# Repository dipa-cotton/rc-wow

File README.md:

# rc-wow
custom RC Car Radio, with an LR1121 for dual-band access! I made this because I have a broken RC Car at my home, and the radio system was quite outdated so having a more enhanced radio system will allow me to control the car from farther away!
## project overview
this project contains an LR1121, ESP32, a microSD card, a USB-C receptacle, a spot for an OLED, and a spot to add a radio antenna, as well as other features to switch between frequencies and control power so it works both battery-powered and when plugged in.
## how it works
It is controlled by an esp32 and lr1121, with the espP32 serving as the microcontroller to take charge of all input and the lr1121 allowing the user to switch between different frequencies. There are ICs for this "switching" function. there is also a USB C receptical for input and control as well as a microSD card to log things that happen. The coax cable port is for the antenna. Resistors, decoupling capacitors, and Schottky diodes are used to prevent the board from exploding. The buttons are for reset and boot. There's an opening for an OLED display.
## pictures

## bom

| Part | Purpose | Qty | Unit Price | Total | Vendor |
|---|---|---:|---:|---:|---|
| [Battery Pack](https://www.aliexpress.us/item/3256807960114360.html) | Battery | 1 | $0.50 | $0.50 | AliExpress |
| [SD Card Reader](https://www.mouser.com/en/ProductDetail/Wurth-Elektronik/693072010801) | SD card reader | 1 | $3.50 | $3.50 | Mouser |
| [USB-C Receptacle](https://www.digikey.com/en/products/detail/gct/USB4085-GF-A/9859662) | USB connection | 1 | $1.00 | $1.00 | DigiKey |
| [Schottky Diode](https://www.aliexpress.us/item/3256808944462819.html) | Signal clearance | 1 | $3.50 | $3.50 | AliExpress |
| [Ferrite Bead](https://www.digikey.com/en/products/detail/laird-signal-integrity-products/28C0236-0JW-10/806596) | Ferrite bead | 1 | $1.10 | $1.10 | DigiKey |
| [0900FM15K0039001E](https://www.digikey.com/en/products/detail/johanson-technology-inc/0900FM15K0039001E/16639329) | Frequency switching | 2 | $0.50 | $1.00 | DigiKey |
| [0900DP15A2450001E](https://www.digikey.com/en/products/detail/johanson-technology-inc/0900DP15A2450001E/7943531) | Frequency switching | 1 | $1.00 | $1.00 | DigiKey |
| [ESP32-S3-WROOM-1-N8R8](https://www.digikey.com/en/products/detail/espressif-systems/ESP32-S3-WROOM-1-N8R8/15295891) | Main controller | 1 | $7.00 | $7.00 | DigiKey |
| [PE4259](https://www.digikey.com/en/products/detail/psemi/4259-63/2614473) | Frequency switching | 3 | $1.00 | $3.00 | DigiKey |
| [XC6220B331MR-G](https://www.digikey.com/en/products/detail/torex-semiconductor-ltd/XC6220B331MR-G/2138177) | Power regulation | 1 | $1.00 | $1.00 | DigiKey |
| [LR1121IMLTRT](https://www.digikey.com/en/products/detail/semtech-corporation/LR1121IMLTRT/17874420) | Frequency switching | 1 | $8.50 | $8.50 | DigiKey |
| [PMOS](https://www.digikey.com/ordering/shoppingcart) | Switching | 1 | $1.00 | $1.00 | DigiKey |
| [Crystals](https://www.digikey.com/en/products/detail/ecs-inc/ECS-320-8-36B-CKY-TR/9838841) | Oscillator | 2 | $1.00 | $2.00 | DigiKey |
| [OLED Display](https://www.aliexpress.us/item/3256812744946971.html) | Display | 1 | $3.00 | $3.00 | AliExpress |
| [Coaxial Cable Connector](https://www.digikey.com/en/products/detail/joymax-electronics/CT-SAD010XM/27545740) | Antenna connector | 1 | $2.50 | $2.50 | DigiKey |
| [Dual-Band Antenna](https://radiomasterrc.com/products/dual-band-2-4ghz-sub-g-900mhz-antenna) | Antenna | 1 | $15.00 | $15.00 | RadioMaster |
| [PCB](https://jlcpcb.com) | PCB for all components | 1 | $13.00 | $13.00 | JLCPCB |
| **Parts Subtotal** | — | — | — | **$67.60** | — |
| **Tax & Shipping** | — | — | — | **$0.00** | — |
| **Grand Total** | — | — | — | **$67.60** | — |
## notes
this should hopefully work! i had to calculate impedance for the RF traces and such, and it should work fine. however, updates may be pushed and future versions may be made :D also i have a HAM radio license so double check that things are legal on your end.

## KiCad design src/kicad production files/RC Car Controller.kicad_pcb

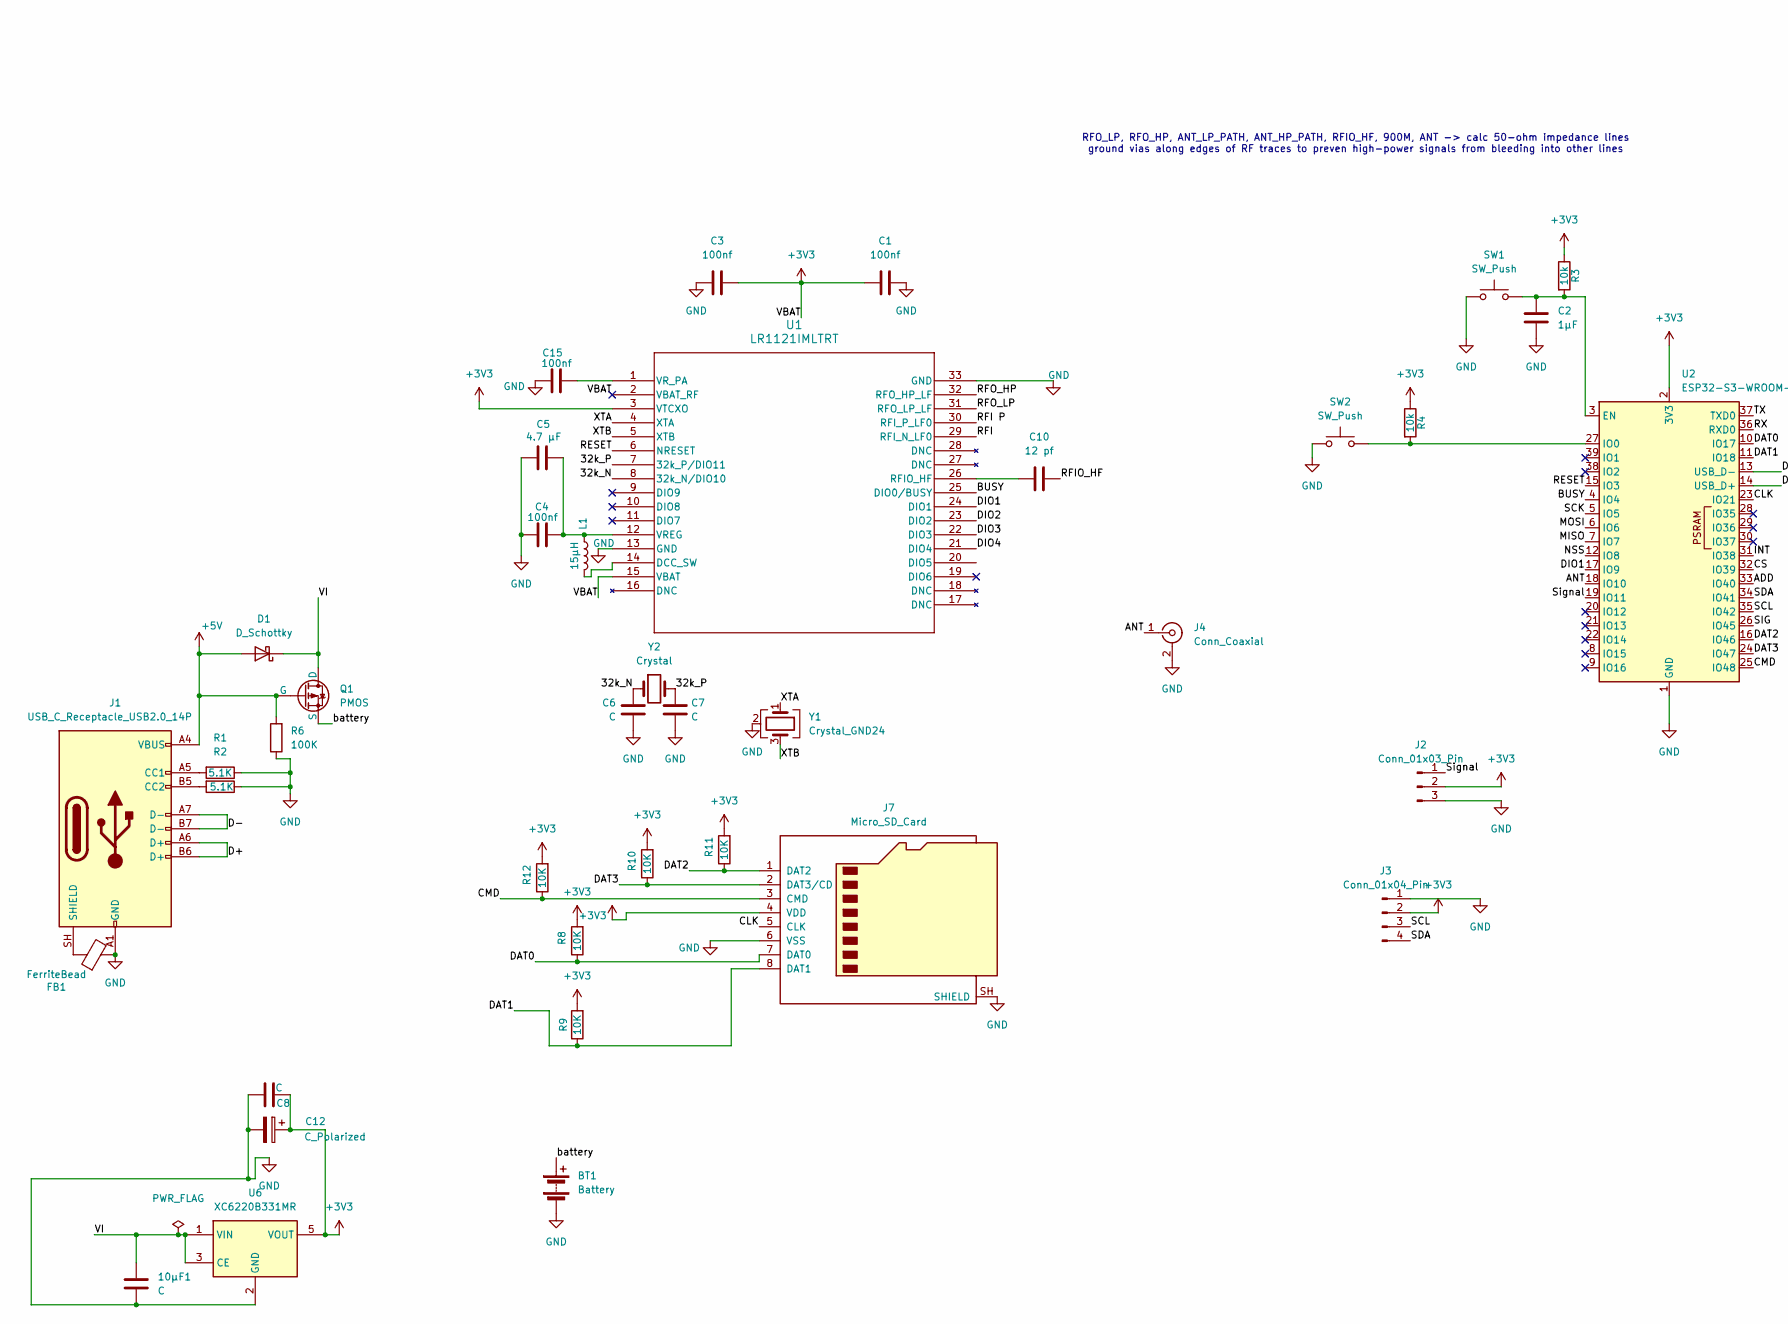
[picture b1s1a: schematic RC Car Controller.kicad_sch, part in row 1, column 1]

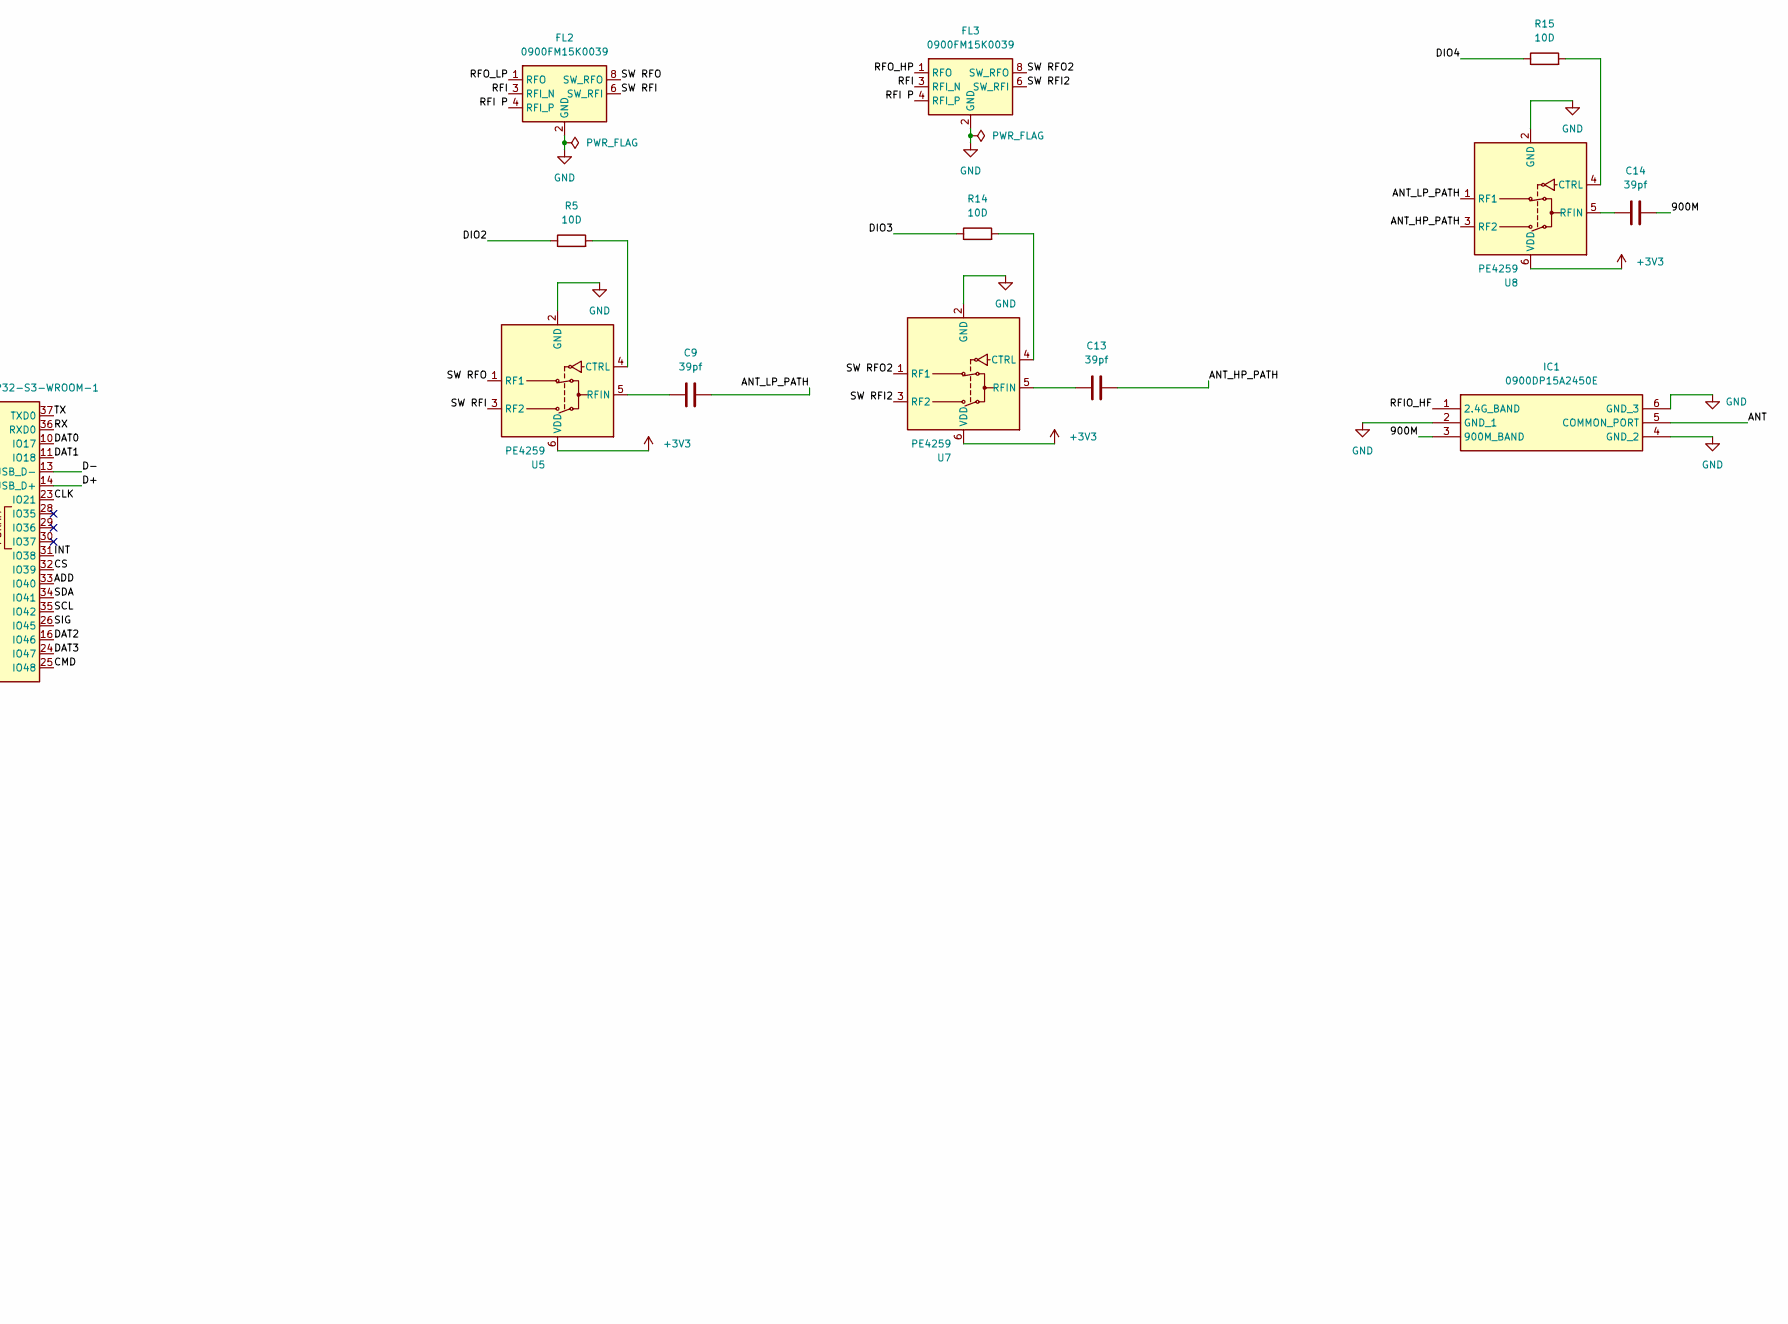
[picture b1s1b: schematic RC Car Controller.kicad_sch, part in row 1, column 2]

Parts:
10µF1: C; C_0402_1005Metric_Pad0.74x0.62mm_HandSolder
BT1: Battery; BatteryHolder_Keystone_2462_2xAA
C1, C3, C4, C15: 100nf; C_0402_1005Metric_Pad0.74x0.62mm_HandSolder
C2: 1µF; C_0402_1005Metric_Pad0.74x0.62mm_HandSolder
C5: 4.7 µF; C_0402_1005Metric_Pad0.74x0.62mm_HandSolder
C6, C7, C8: C; C_0402_1005Metric_Pad0.74x0.62mm_HandSolder
C9, C13, C14: 39pf; C_0402_1005Metric_Pad0.74x0.62mm_HandSolder
C10: 12 pf; C_0402_1005Metric_Pad0.74x0.62mm_HandSolder
C12: C_Polarized; C_Radial_D6.3mm_H7.0mm_P2.50mm
D1: D_Schottky; D_A-405_P10.16mm_Horizontal
FB1: FerriteBead; LairdTech_28C0236-0JW-10
FL2, FL3: 0900FM15K0039; Balun_Johanson_0900FM15K0039
IC1: 0900DP15A2450E; Mouser Part Number 609-0900DP15A2450E
J1: USB_C_Receptacle_USB2.0_14P; USB_C_Receptacle_GCT_USB4085
J2: Conn_01x03_Pin; PinHeader_1x03_P2.54mm_Vertical
J3: Conn_01x04_Pin; PinHeader_1x04_P1.00mm_Vertical
J4: Conn_Coaxial; BNC_TEConnectivity_1478204_Vertical
J7: Micro_SD_Card; microSD_HC_Wuerth_693072010801
L1: 15µH; PinHeader_1x02_P1.00mm_Vertical
Q1: PMOS; SOT-23_Handsoldering
R1, R2: 5.1K; R_0402_1005Metric_Pad0.72x0.64mm_HandSolder
R3, R4: 10k; R_0402_1005Metric_Pad0.72x0.64mm_HandSolder
R5, R14, R15: 10D; R_0603_1608Metric
R6: 100K; R_0603_1608Metric
R8, R9, R10, R11, R12: 10K; R_0603_1608Metric
SW1, SW2: SW_Push; SW_Push_1P1T_NO_CK_PTS125Sx43SMTR
U1: LR1121IMLTRT; QFN32_5X5_MLP_SEM
U2: ESP32-S3-WROOM-1
U5, U7, U8: PE4259; SOT-363_SC-70-6
U6: XC6220B331MR; SOT-23-5
Y1: Crystal_GND24; Crystal_SMD_SeikoEpson_FA128-4Pin_2.0x1.6mm
Y2: Crystal; Crystal_SMD_Qantek_QC5CB-2Pin_5x3.2mm

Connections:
+3V3: C1.1, C3.2, C8.1, C12.1, J2.2, J3.2, J7.4 (VDD), R3.1, R4.1, R8.2, R9.2, R10.2, R11.2, R12.2, U1.2 (VBAT_RF), U1.3 (VTCXO), U1.15 (VBAT), U2.2 (3V3), U5.6 (VDD), U6.5 (VOUT), U7.6 (VDD), U8.6 (VDD)
+5V: D1.2 (A), J1.A4 (VBUS), J1.A9 (VBUS), J1.B4 (VBUS), J1.B9 (VBUS), Q1.2 (G), R6.2
/32k_N: C6.1, U1.8 (32k_N/DIO10), Y2.1
/32k_P: C7.1, U1.7 (32k_P/DIO11), Y2.2
/900M: C14.1, IC1.3 (900M_BAND)
/ADD: U2.33 (IO40)
/ANT: IC1.5 (COMMON_PORT), J4.1 (In), U2.18 (IO10)
/ANT_HP_PATH: C13.1, U8.3 (RF2)
/ANT_LP_PATH: C9.1, U8.1 (RF1)
/BUSY: U1.25 (DIO0/BUSY), U2.4 (IO4)
/CLK: J7.5 (CLK), U2.23 (IO21)
/CMD: J7.3 (CMD), R12.1, U2.25 (IO48)
/CS: U2.32 (IO39)
/D+: J1.A6 (D+), J1.B6 (D+), U2.14 (USB_D+)
/D-: J1.A7 (D-), J1.B7 (D-), U2.13 (USB_D-)
/DAT0: J7.7 (DAT0), R8.1, U2.10 (IO17)
/DAT1: J7.8 (DAT1), R9.1, U2.11 (IO18)
/DAT2: J7.1 (DAT2), R11.1, U2.16 (IO46)
/DAT3: J7.2 (DAT3/CD), R10.1, U2.24 (IO47)
/DIO1: U1.24 (DIO1), U2.17 (IO9)
/DIO2: R5.1, U1.23 (DIO2)
/DIO3: R14.1, U1.22 (DIO3)
/DIO4: R15.1, U1.21 (DIO4)
/INT: U2.31 (IO38)
/MISO: U2.7 (IO7)
/MOSI: U2.6 (IO6)
/NSS: U2.12 (IO8)
/RESET: U1.6 (NRESET), U2.15 (IO3)
/RFI: FL2.3 (RFI_N), FL3.3 (RFI_N), U1.29 (RFI_N_LF0)
/RFI P: FL2.4 (RFI_P), FL3.4 (RFI_P), U1.30 (RFI_P_LF0)
/RFIO_HF: C10.2, IC1.1 (2.4G_BAND)
/RFO_HP: FL3.1 (RFO), U1.32 (RFO_HP_LF)
/RFO_LP: FL2.1 (RFO), U1.31 (RFO_LP_LF)
/RX: U2.36 (RXD0)
/SCK: U2.5 (IO5)
/SCL: J3.3, U2.35 (IO42)
/SDA: J3.4, U2.34 (IO41)
/SIG: U2.26 (IO45)
/SW RFI: FL2.6 (SW_RFI), U5.3 (RF2)
/SW RFI2: FL3.6 (SW_RFI), U7.3 (RF2)
/SW RFO: FL2.8 (SW_RFO), U5.1 (RF1)
/SW RFO2: FL3.8 (SW_RFO), U7.1 (RF1)
/Signal: J2.1, U2.19 (IO11)
/TX: U2.37 (TXD0)
/VI: 10µF1.1, D1.1 (K), Q1.1 (D), U6.1 (VIN), U6.3 (CE)
/XTA: U1.4 (XTA), Y1.1
/XTB: U1.5 (XTB), Y1.3
/battery: BT1.1 (+), Q1.3 (S)
GND: 10µF1.2, BT1.2 (-), C1.2, C2.2, C3.1, C4.2, C5.2, C6.2, C7.2, C8.2, C12.2, C15.2, FB1.2, FL2.2 (GND), FL2.5 (GND), FL2.7 (GND), FL2.9 (GND), FL2.10 (GND), FL3.2 (GND), FL3.5 (GND), FL3.7 (GND), FL3.9 (GND), FL3.10 (GND), IC1.2 (GND_1), IC1.4 (GND_2), IC1.6 (GND_3), J1.A1 (GND), J1.A12 (GND), J1.B1 (GND), J1.B12 (GND), J2.3, J3.1, J4.2 (Ext), J7.6 (VSS), J7.SH (SHIELD), R1.1, R2.1, R6.1, SW1.1, SW2.1, U1.13 (GND), U1.33 (GND), U2.1 (GND), U2.40 (GND), U2.41 (GND), U5.2 (GND), U6.2 (GND), U7.2 (GND), U8.2 (GND), Y1.2 (G), Y1.4 (G)
unnamed: J1.A5 (CC1), R1.2
unnamed: J1.B5 (CC2), R2.2
unnamed: FB1.1, J1.SH (SHIELD)
unnamed: L1.2, U1.14 (DCC_SW)
unnamed: C10.1, U1.26 (RFIO_HF)
unnamed: C4.1, C5.1, L1.1, U1.12 (VREG)
unnamed: C15.1, U1.1 (VR_PA)
unnamed: C2.1, R3.2, SW1.2, U2.3 (EN)
unnamed: R4.2, SW2.2, U2.27 (IO0)
unnamed: R5.2, U5.4 (CTRL)
unnamed: C9.2, U5.5 (RFIN)
unnamed: R14.2, U7.4 (CTRL)
unnamed: C13.2, U7.5 (RFIN)
unnamed: R15.2, U8.4 (CTRL)
unnamed: C14.2, U8.5 (RFIN)

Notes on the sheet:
RFO_LP, RFO_HP, ANT_LP_PATH, ANT_HP_PATH, RFIO_HF, 900M, ANT -> calc 50-ohm impedance lines ground vias along edges of RF traces to preven high-power signals from bleeding into other lines

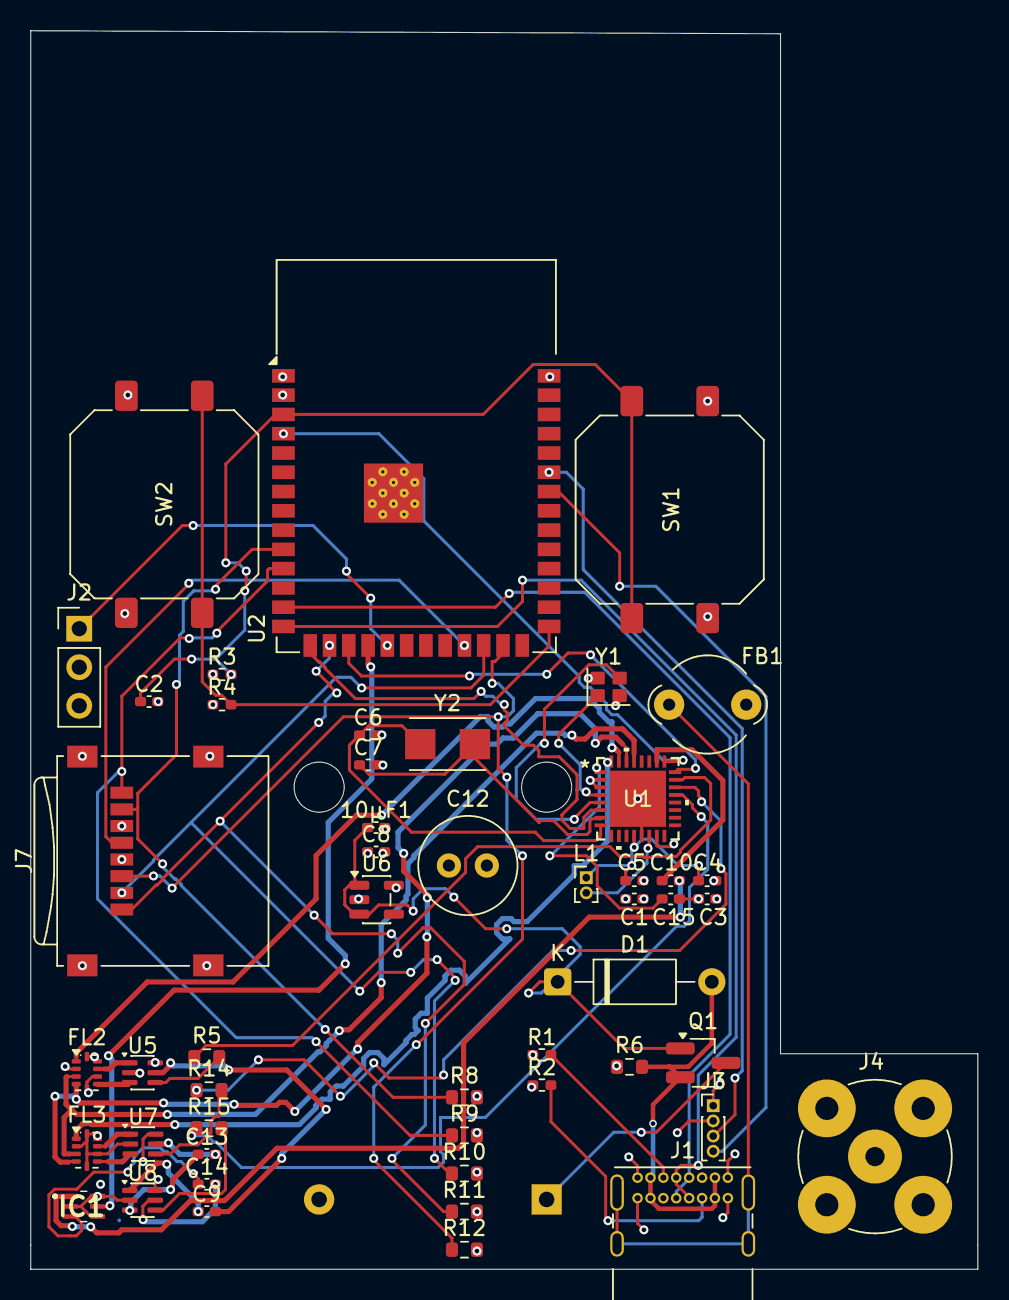
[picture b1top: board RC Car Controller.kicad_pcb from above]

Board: 4 copper layers, 62.4 x 81.6 mm, 51 parts (1 on the bottom side), 54 nets.
